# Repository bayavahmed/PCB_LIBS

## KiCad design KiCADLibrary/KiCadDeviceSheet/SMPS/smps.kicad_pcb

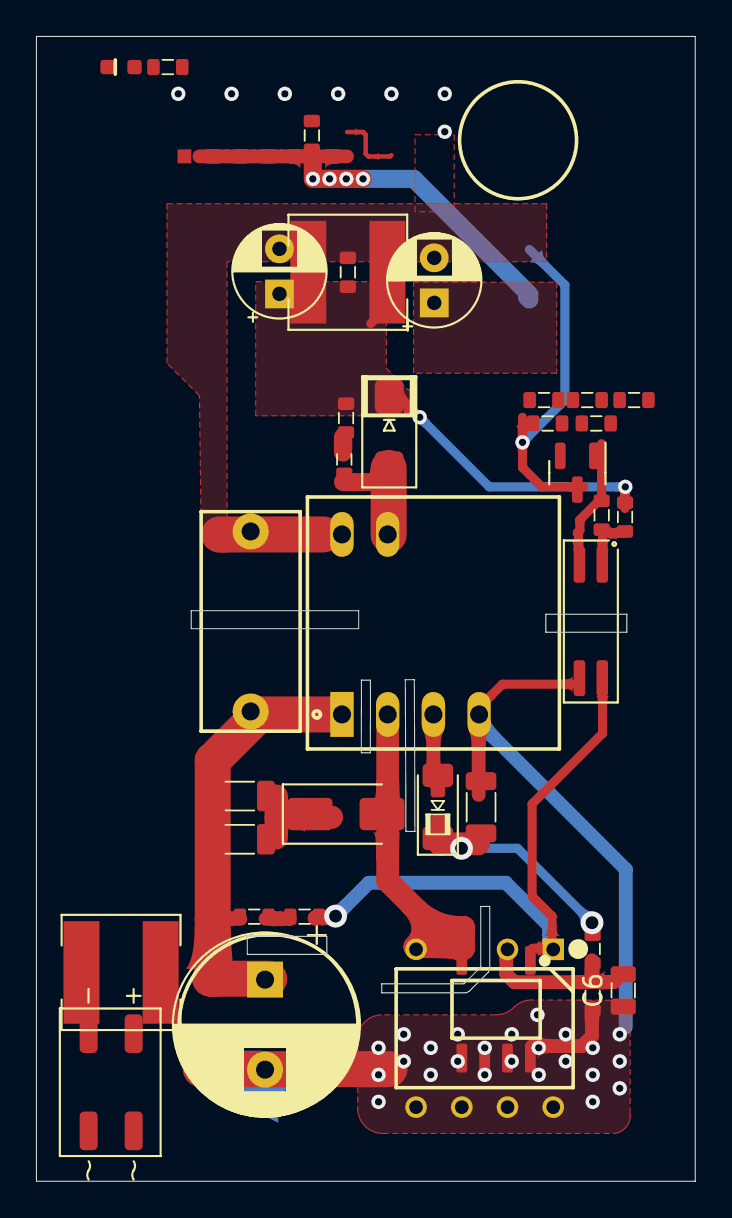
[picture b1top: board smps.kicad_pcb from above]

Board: 2 copper layers, 36.6 x 63.6 mm, 37 parts (0 on the bottom side), 20 nets.

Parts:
C1: 10uF/4000VDC; CP_Radial_D10.0mm_P5.00mm
C2: 10nF/500V; C_1206_3216Metric_Per
C3: 10uF / 25V; C_1206_3216Metric_Per
C4, C9, C13: 100nF; C_0603_1608Metric_Per
C5: 2.2nF/2000V; CAP-Y1 10mm
C6: 10uF; C_0805_2012Metric_Per
C7: 470pF; C_0603_1608Metric_Per
C8, C12: 100uF; CP_Radial_D5.0mm_P2.50mm
C10: 10nF; C_0603_1608Metric_Per
C11: 1uF; C_0603_1608Metric_Per
D1: US1M; D_SMA
D2: LL4148; D_MiniMELF
D3: 1N4148WS; SOD-323F_Per
D4: SS26; D_SMA_Per
D5: LED_RED; LED_0603_1608Metric_Per
D6: MB10S; Diode_Bridge_MBS
L1: 1mH/100mA; L_6x6_SMD
L2: 22uH/0.7A; L_6x6_SMD
OC1: LTV-217; SO-4_4.4x2.3mm_P1.27mm
R1: 220kΩ; R_1206_3216Metric_Per
R2: 16.9kΩ; R_0603_1608Metric_Per
R3, R4: 2MΩ; R_0603_1608Metric_Per
R5: 75Ω; R_0603_1608Metric_Per
R6: 220Ω; R_0603_1608Metric_Per
R7: 1kΩ; R_0603_1608Metric_Per
R8: 100Ω/%1; R_0603_1608Metric_Per
R9: 6.04kΩ/%1; R_0603_1608Metric_Per
R10: 1.58kΩ/%1; R_0603_1608Metric_Per
R11: 10kΩ; R_0603_1608Metric_Per
T1: smps_trafo_3Winding_TNY284; SMPS_Trafo_3Winding - TNY284
U1: TNY284D; TNY284D_SMD
U2: TNY284PG
U3: TL431DBZ; SOT-23

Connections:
+12V: C11.2, C12.1, C13.2, L2.2, R9.1, R11.2
GND: C5.1, C8.2, C11.1, C12.2, C13.1, D5.1 (K), R10.2, T1.10, U3.3 (A)
GNDPWR: C1.2, C3.2, C4.1, C6.1, OC1.3, T1.4, U1.5 (S), U2.5 (S)
unnamed: C7.2, R5.2
unnamed: C10.2, R8.2
unnamed: D1.2 (A), T1.2, U1.4 (D), U2.4 (D)
unnamed: C2.2, D1.1 (K), R1.1
unnamed: D2.2 (A), D3.2 (A), T1.3
unnamed: D4.2 (A), R5.1, T1.9
unnamed: C7.1, C8.1, D4.1 (K), L2.1, R6.1
unnamed: D5.2 (A), R11.1
unnamed: D6.1 (+), L1.1
unnamed: OC1.1, R6.2, R7.1
unnamed: R3.2, R4.1
unnamed: C4.2, C6.2, R2.1, U1.2 (BP/M), U2.2 (BP/M)
unnamed: OC1.4, R4.2, U1.1 (EN/UV), U2.1 (EN/UV)
unnamed: C9.2, OC1.2, R7.2, R8.1, U3.1 (K)
unnamed: C9.1, C10.1, R9.2, R10.1, U3.2 (REF)
VCC: C3.1, D2.1 (K), D3.1 (K), R2.2
VDC: C1.1, C2.1, C5.2, L1.2, R1.2, R3.1, T1.1

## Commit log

2025-12-09 pcb kutuphaneleri birleştirildi
2025-12-14 slide switch eklendi. step modeli eklendi
2025-12-22 eklemeler
2025-12-30 bikaç değişikler
2026-01-03 MCP3911 eklendi
2026-01-04 kicad MCP3911 düzeltme
2026-01-18 usb extender ve konnektör
2026-03-17 rakorlu kutu eklendi. RF shield düzenlendi.
